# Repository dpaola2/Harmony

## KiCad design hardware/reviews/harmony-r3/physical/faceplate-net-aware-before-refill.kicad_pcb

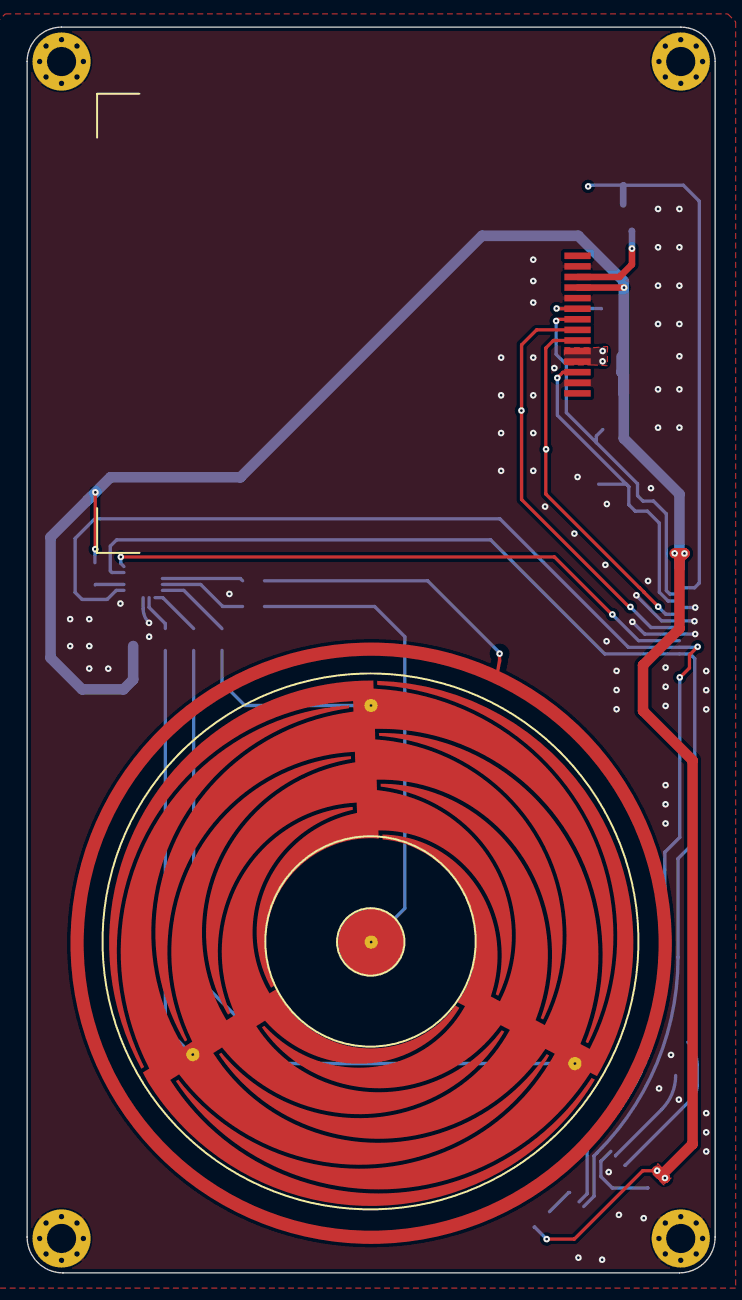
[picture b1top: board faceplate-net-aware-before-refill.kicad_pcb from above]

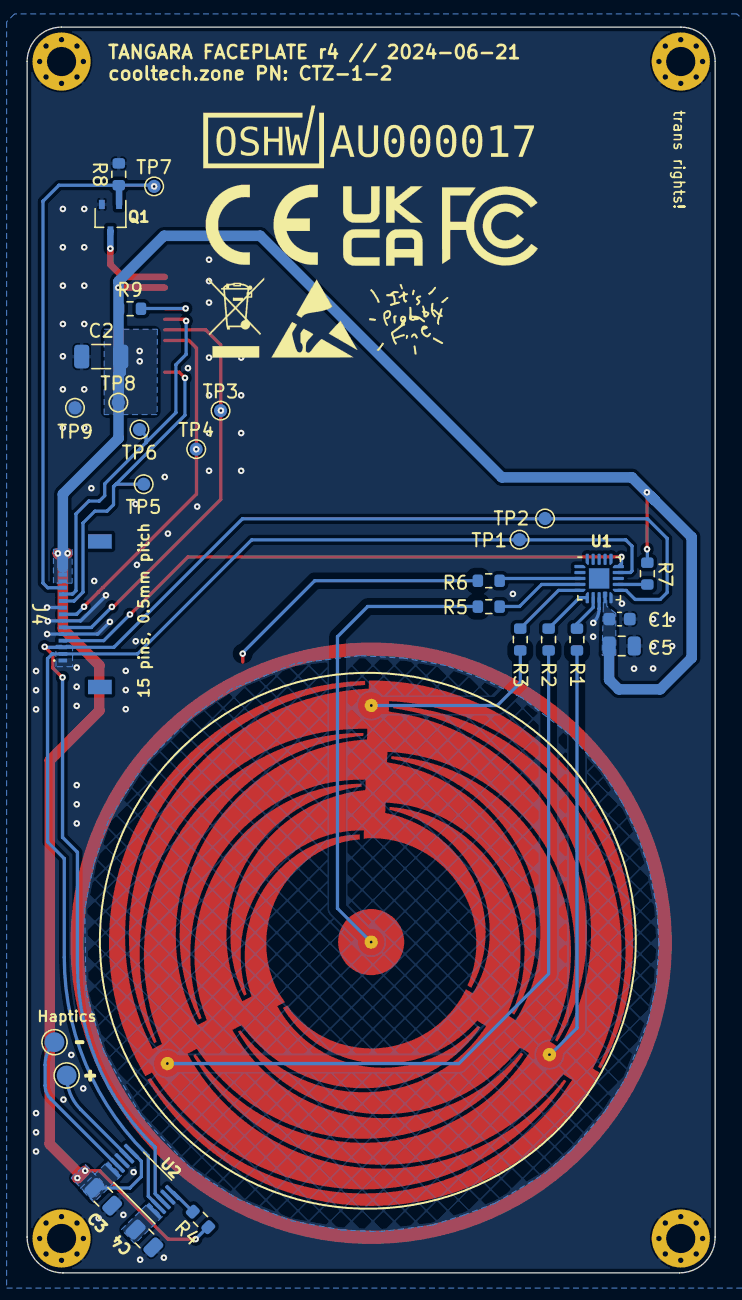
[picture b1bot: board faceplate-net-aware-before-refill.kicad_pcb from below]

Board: 2 copper layers, 52.0 x 94.2 mm, 39 parts (31 on the bottom side), 27 nets.

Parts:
C1: 0.1uF; C_0603_1608Metric
C2: 22uF; C_1206_3216Metric
C3, C4, C5: 1uF; C_0805_2012Metric
H1, H2, H3, H4: MountingHole; MountingHole_2.2mm_M2_Pad_Via
J1: +; TestPoint_Pad_D1.5mm
J2: -; TestPoint_Pad_D1.5mm
J4: MB Connector; G-Switch GT-F0509SR15-15SMT01
LCD1: JD-T1800
Q1: PJC138K; SOT-323_SC-70
R1, R2, R3, R4, R5, R6, R7, R9: 10k; R_0603_1608Metric
R8: 1M; R_0603_1608Metric
SW1: BUTTON; qtouch-button
SW2: WHEEL; qtouch-wheel
SW3: GUARD; qtouch-guard
TP1: SCL; TestPoint_Pad_D1.0mm
TP2: SDA; TestPoint_Pad_D1.0mm
TP3: PICO; TestPoint_Pad_D1.0mm
TP4: SCLK; TestPoint_Pad_D1.0mm
TP5: CS; TestPoint_Pad_D1.0mm
TP6: RS; TestPoint_Pad_D1.0mm
TP7: LED; TestPoint_Pad_D1.0mm
TP8: 3V3; TestPoint_Pad_D1.0mm
TP9: GND; TestPoint_Pad_D1.0mm
U1: AT42QT2120; VQFN-20-1EP_3x3mm_P0.45mm_EP1.55x1.55mm
U2: DRV2605LDGS; VSSOP-10_3x3mm_P0.5mm
kibuzzard-63E31E51: G***; kibuzzard-63E31E51
kibuzzard-63E31E57: G***; kibuzzard-63E31E57

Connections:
+3V3: C1.1, C2.1, C3.2, C5.2, J4.13, J4.14, J4.15, LCD1.4 (LEDA), LCD1.10 (VCC), LCD1.11 (VCC2), R4.1, R7.2, R9.1, TP8.1, U1.9 (VDD), U2.6 (VDD/NC), U2.10 (VDD)
/CS: J4.10, LCD1.12 (CS), TP5.1
/LED_ENABLE: J4.12, Q1.1 (G), R8.1, TP7.1
/PICO: J4.6, LCD1.8 (DATA), TP3.1
/RS: J4.11, LCD1.7 (RS/DC), TP6.1
/SCL: J4.2, TP1.1, U1.14 (SCL), U2.2 (SCL)
/SCLK: J4.8, LCD1.9 (CLOCK), TP4.1
/SDA: J4.3, TP2.1, U1.11 (SDA), U2.3 (SDA)
/TOUCH_INT: J4.4, U1.15 (~CHANGE)
GND: C1.2, C2.2, C3.1, C4.1, C5.1, H1.1, H2.1, H3.1, H4.1, J4.1, J4.5, J4.7, J4.9, LCD1.2 (GND), LCD1.5 (GND1), LCD1.13 (GND2), Q1.2 (S), R8.2, TP9.1, U1.8 (VSS), U1.10 (MODE), U2.4 (IN/TRIG), U2.8 (GND)
unnamed: J1.1, U2.7 (OUT+)
unnamed: J2.1, U2.9 (OUT-)
unnamed: LCD1.3 (LEDK), Q1.3 (D)
unnamed: LCD1.6 (RESET), R9.2
unnamed: R5.1, SW1.1
unnamed: R1.1, SW2.1
unnamed: R2.1, SW2.2
unnamed: R3.1, SW2.3
unnamed: R6.1, SW3.1
unnamed: R1.2, U1.7 (KEY0)
unnamed: R2.2, U1.6 (KEY1)
unnamed: R3.2, U1.5 (KEY2)
unnamed: R5.2, U1.4 (KEY3)
unnamed: R6.2, U1.3 (KEY4)
unnamed: R7.1, U1.12 (~RESET)
unnamed: R4.2, U2.5 (EN)
unnamed: C4.2, U2.1 (REG)

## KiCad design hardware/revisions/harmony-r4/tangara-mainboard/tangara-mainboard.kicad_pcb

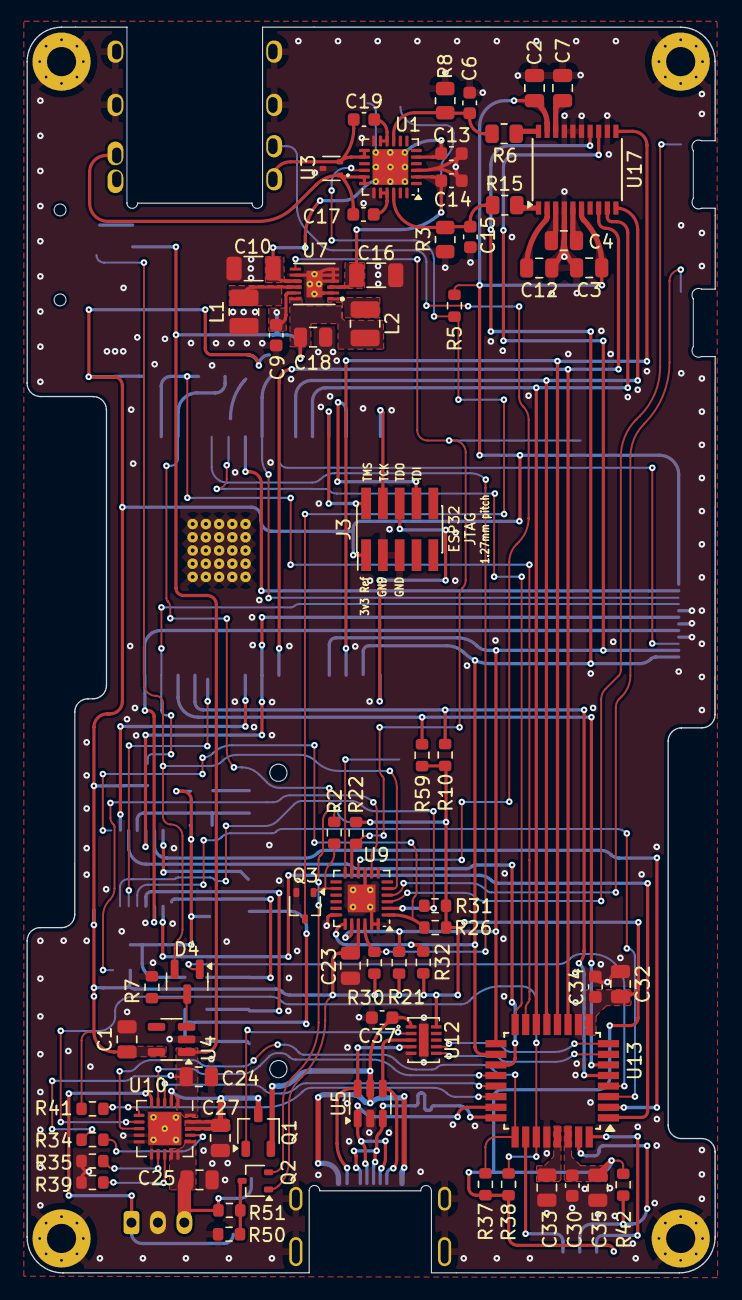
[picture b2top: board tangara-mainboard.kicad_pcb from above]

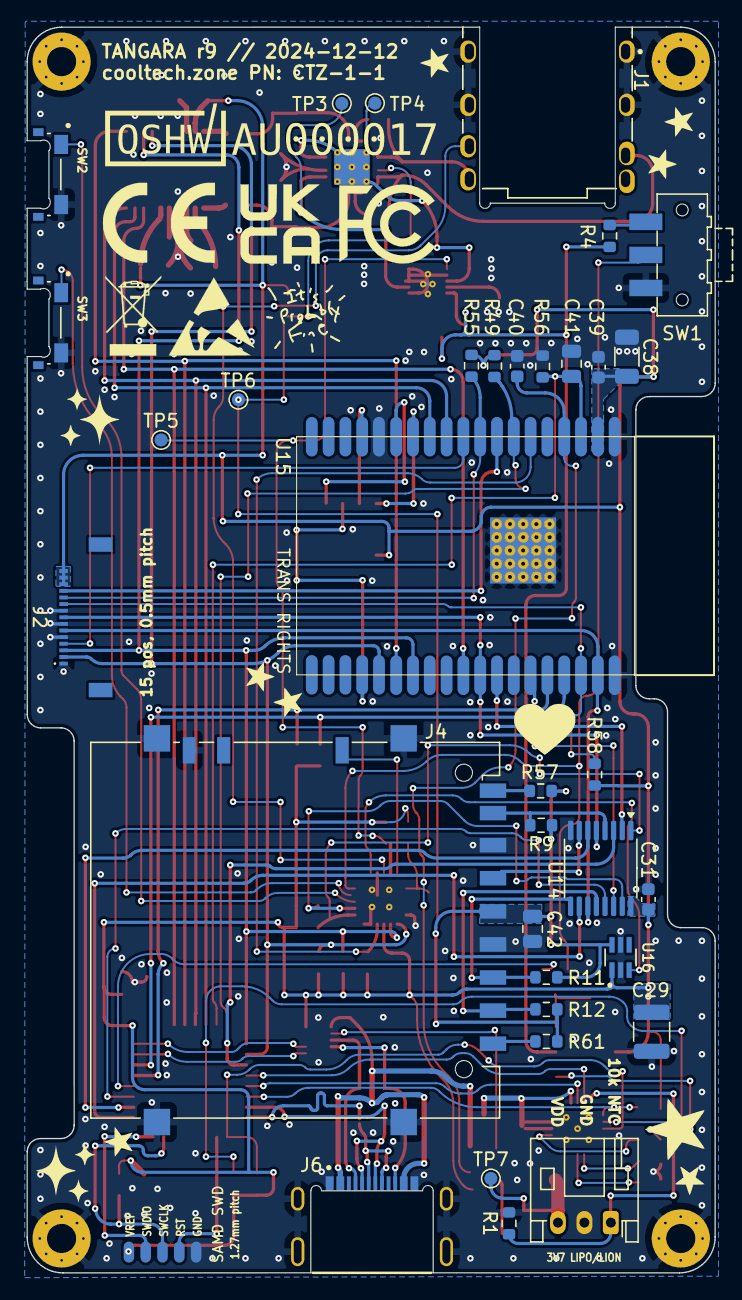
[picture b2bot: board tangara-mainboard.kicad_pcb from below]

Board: 4 copper layers, 52.0 x 94.2 mm, 106 parts (35 on the bottom side), 92 nets.

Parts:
C1, C2, C3, C7, C18, C24, C25, C27, C32, C35, C42: 10μF; C_0805_2012Metric
C4, C12, C23, C33, C41: 1μF; C_0805_2012Metric
C6, C15: 2700pF; C_0603_1608Metric
C9, C13, C14, C30, C31, C34, C37, C39, C40: 0.1μF; C_0603_1608Metric
C10, C16, C38: 22μF; C_1206_3216Metric
C17, C19: 100pF; C_0603_1608Metric
C29: 100uF; C_1210_3225Metric
D4: BAT54C; SOT-23
H1, H2, H3, H4: MountingHole; MountingHole_2.2mm_M2_Pad_Via2
J1: SJ-3506-SMT; CUI_SJ-3506-SMT
J2: FP Connector; G-Switch GT-F0509SR15-15SMT01
J3: JTAG; PinHeader_2x05_P1.27mm_Vertical_SMD
J4: SD_Card; SD_Hirose_DM1AA_SF_PEJ82
J5: SWD; SAMDSWD
J6: USB; GCT_USB4510-03-1-A_REVA
J7: Battery; JST_PH_S3B-PH-K_1x03_P2.00mm_Horizontal
L1, L2: 4.7μH; L_1008_2520Metric
Q1: PMV48XPA2R; TSOT-23
Q2, Q3: PJC138K; SOT-323_SC-70
R1, R2, R4, R5, R9, R10, R11, R12, R21, R22, R26, R30, R31, R32, R34, R35, R37, R38, R41, R49, R55, R57, R58, R59, R61: 10kΩ; R_0603_1608Metric
R3, R8: 2.2kΩ; R_0805_2012Metric
R6, R15: 560Ω; R_0805_2012Metric
R7, R50, R51, R56: 1MΩ; R_0603_1608Metric
R39, R42: 1kΩ; R_0603_1608Metric
SW1: SW_SPDT; SW_SPDT_CK-JS102011SAQN
SW2, SW3: SW_Push; SW_EVQ-P4HB3B
TP3: +5V; TestPoint_Pad_D1.0mm
TP4: -5V; TestPoint_Pad_D1.0mm
TP5: AMP_EN; TestPoint_Pad_D1.0mm
TP6: AMP_MUTE; TestPoint_Pad_D1.0mm
TP7: BAT; TestPoint_Pad_D1.0mm
U1: INA1620; QFN-24-1EP_4x4mm_P0.5mm_EP2.7x2.7mm_ThermalVias
U3: D5V0L2B3T-7; SOT-523
U4: TLV75533PDBV; SOT-23-5
U5: PE1605C4A6; SOT-23-6
U7: TPS65133; SON40P300X300X80-13N
U9: PCA8575; HVQFN-24-1EP_4x4mm_P0.5mm_EP2.1x2.1mm
U10: MCP73871; QFN-20-1EP_4x4mm_P0.5mm_EP2.5x2.5mm_ThermalVias2
U12: BD91N01NUX; BD91N01NUX-E2
U13: ATSAMD21E18A-AF; TQFP-32_7x7mm_P0.8mm
U14: 74CBTLV3257; TSSOP-16_4.4x5mm_P0.65mm
U15: ESP32-WROVER-E; ESP32-WROVER
U16: TPS22948; SOT65P210X110-6N
U17: WM8523; SSOP-20_4.4x6.5mm_P0.65mm

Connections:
3.5mm_DETECT: J1.4, U9.10 (IO1_0)
+3V3: C1.1, C2.2, C3.1, C23.1, C29.1, C30.1, C31.1, C32.2, C34.1, C35.2, C38.1, C39.1, J2.13, J2.14, J2.15, J3.1 (vRef), J5.1, Q2.1 (G), R2.2, R5.1, R10.1, R21.1, R22.2, R26.1, R30.1, R31.1, R32.1, R37.1, R38.1, R41.1, R42.1, R49.1, R55.1, R58.1, R59.1, U4.5 (OUT), U9.21 (VDD), U12.10 (VDD_IO), U13.9 (VDDANA), U13.30 (VDDIN), U14.16 (VCC), U15.2 (VDD), U16.1 (IN), U17.6 (LINEVDD), U17.19 (AVDD)
+5VA: C14.1, C16.1, TP3.1, U1.2 (V+), U7.3 (VPOS)
-5VA: C10.2, C13.1, TP4.1, U1.5 (V-), U1.25 (EP), U7.9 (VNEG)
/ESP_EN: C41.1, R56.2, U13.15 (PA14), U15.3 (EN)
/JTAG.TCK: J3.4 (TCK), U15.16 (JTAG.TCK)
/JTAG.TDI: J3.8 (TDI), U15.14 (JTAG.TDI)
/JTAG.TDO: J3.6 (TDO), U15.23 (JTAG.TDO)
/JTAG.TMS: J3.2 (TMS), U15.13 (JTAG.TMS)
/Power/NTC: J7.1, R1.1, U10.5 (THERM)
/Power/VBUS_SWITCHED: C27.1, Q1.3 (D), U10.2 (VPCC), U10.18 (IN), U10.19 (IN)
/SWD.RESET: J5.4, U13.26 (~RESET)
/SWD.SWCLK: J5.3, R42.2, U13.31 (SWCLK)
/SWD.SWDIO: J5.2, U13.32 (SWDIO)
/UART.ESP.RX: R10.2, U13.5 (PA04(SERCOM0.0)), U15.34 (UART.RX)
/UART.ESP.TX: R59.2, U13.6 (PA05(SERCOM0.1)), U15.35 (UART.TX)
/~SAMD_INT: R49.2, U13.16 (PA15), U15.7 (I35)
AMP_EN: R22.1, TP5.1, U7.7 (EN), U9.11 (IO1_1)
AMP_MUTE: Q3.3 (D), R5.2, TP6.1, U1.16 (EN)
BAT_LEVEL: C40.2, Q2.2 (S), U15.4 (ADC1_CH0/NOINT)
CHG_PROG: U10.4 (PROG2), U13.20 (PA19)
CHG_SEL: U10.3 (SEL), U13.21 (PA22)
CHG_STAT1: R37.2, U10.8 (STAT1/~LBO), U13.25 (PA27)
CHG_STAT2: R38.2, U10.7 (STAT2), U13.27 (PA28)
DAC.BCK: U13.13 (PA10(I2S/SCK)), U15.11 (I2S.BCK), U17.10 (BCLK)
DAC.DATA: U13.11 (PA08(I2S/SD)), U15.29 (I2S.DOUT), U17.8 (DACDAT)
DAC.LRCK: U13.14 (PA11(IS2/FS)), U15.12 (I2S.LRCK), U17.9 (LRCLK)
DAC.MCK: U13.12 (PA09(I2S/MCK)), U15.25 (BOOT/I2S.SCK), U17.11 (MCLK)
DISPLAY_DR: J2.11, R55.2, U15.9 (IO33)
DISPLAY_LED_EN: J2.12, U15.8 (IO32)
ESP_SPI.DISPLAY_CS: J2.10, R58.2, U15.36 (SPI.CS1)
ESP_SPI.PICO: J2.6, U14.11, U15.37 (SPI.PICO)
ESP_SPI.POCI: U14.2, U15.31 (SPI.POCI)
ESP_SPI.SCLK: J2.8, U14.5, U15.30 (SPI.CLK)
ESP_SPI.SD_CS: U14.14, U15.33 (SPI.CS0)
GND: C1.2, C2.1, C3.2, C6.1, C7.2, C9.2, C10.1, C12.1, C13.2, C14.2, C15.1, C16.2, C18.2, C23.2, C24.2, C25.2, C27.2, C29.2, C30.2, C31.2, C32.1, C33.1, C34.2, C35.1, C37.2, C38.2, C39.2, C40.1, C41.2, C42.2, H1.1, H2.1, H3.1, H4.1, J1.1, J1.5, J1.SH1, J1.SH2, J2.1, J2.5, J2.7, J2.9, J3.3 (GND), J3.5 (GND), J4.3 (VSS), J4.6 (VSS), J4.SH, J4.SW, J5.5, J6.A1_B12 (GND), J6.B1_A12 (GND), J6.S1 (SHELL_GND), J6.S2 (SHELL_GND), J6.S3 (SHELL_GND), J6.S4 (SHELL_GND), J7.2, L1.1, Q3.2 (S), R1.2, R3.1, R7.1, R8.1, R35.2, R39.2, R50.2, R56.1, SW1.1 (A), SW2.2, SW3.2, U1.3 (GND), U1.12, U1.19, U3.3, U4.2 (GND), U5.2 (GND), U7.2 (PGND), U7.4 (GND), U7.5 (AGND), U7.6 (GND), U7.8 (GND), U7.13 (EXP), U9.9 (VSS), U9.18 (A0), U9.23 (A1), U9.24 (A2), U9.25 (EP), U10.9 (~TE), U10.10 (V_{SS}), U10.11 (V_{SS}), U10.21 (V_{SS}), U12.5 (GND), U12.11 (EP), U13.10 (GND), U13.28 (GND), U14.8 (GND), U15.1 (GND), U15.15 (GND), U15.38 (GND), U15.39 (GND), U16.2 (GND), U16.5 (FLT), U17.4 (LINEGND), U17.12 (SDOUT/DEEMPH), U17.15 ({~CS}/{~MUTE}), U17.16 (CIFMODE), U17.17 (AGND)
I2C.SCL: J2.2, R26.2, U9.19 (SCL), U13.18 (PA17(SERCOM3.1)), U15.24 (I2C.SCL), U17.14 (SCLK)
I2C.SDA: J2.3, R21.2, U9.20 (SDA), U13.17 (PA16(SERCOM3.0)), U15.26 (I2C.SDA), U17.13 (SDA)
KEY_LOCK: D4.2, SW1.2 (B), U9.5 (IO0_4)
KEY_VOL_DOWN: SW3.1, U9.4 (IO0_3)
KEY_VOL_UP: SW2.1, U9.3 (IO0_2)
unnamed: C17.2, J1.2, U1.17, U1.18, U3.1
unnamed: C19.2, J1.3, U1.13, U1.14, U3.2
unnamed: J4.1 (CD/DAT3), R12.2, U14.12
unnamed: J4.5 (CLK), U14.7
unnamed: J4.2 (CMD), R11.2, U14.9
unnamed: J4.7 (DAT0), R9.2, U14.4
unnamed: J4.8 (DAT1), R57.2
unnamed: J4.9 (DAT2), R61.2
unnamed: C42.1, J4.4 (VDD), R9.1, R11.1, R12.1, R57.1, R61.1, U16.6 (OUT)
unnamed: J6.A5 (CC1), U5.4 (IO3), U12.3 (CC1)
unnamed: J6.B5 (CC2), U5.6 (IO5), U12.4 (CC2)
unnamed: C25.1, J7.3, R51.1, TP7.1, U10.14 (V_{BAT}), U10.15 (V_{BAT}), U10.16 (V_{BAT_SENSE})
unnamed: Q1.1 (G), U12.2 (SWDRV)
unnamed: Q2.3 (D), R50.1, R51.2
unnamed: Q3.1 (G), R2.1, U9.14 (IO1_4)
unnamed: R4.1, SW1.3 (C)
unnamed: C15.2, R3.2, R15.2, U1.22 (+)
unnamed: C17.1, U1.20, U1.21 (-)
unnamed: C6.2, R6.2, R8.2, U1.9 (+)
unnamed: C19.1, U1.10 (-), U1.11
unnamed: D4.3, R7.2, U4.3 (EN)
unnamed: L1.2, U7.10 (SWN)
unnamed: L2.1, U7.1 (SWP)
unnamed: R34.2, U10.17 (CE)
unnamed: R39.1, U10.13 (PROG1)
unnamed: R35.1, U10.12 (PROG3)
unnamed: C33.2, U13.29 (VDDCORE)
unnamed: R32.2, U9.1 (IO0_0), U14.1 (S)
unnamed: R31.2, U9.2 (IO0_1), U14.15 (~OE)
unnamed: C4.1, U17.5 (CPCA)
unnamed: C4.2, U17.3 (CPCB)
unnamed: C12.2, U17.2 (CPVOUTN)
unnamed: R15.1, U17.1 (LINEVOUTL)
unnamed: R6.1, U17.20 (LINEVOUTR)
unnamed: C7.1, U17.18 (VMID)
SAMD_SPI.CS: U13.3 (PA02), U14.13
SAMD_SPI.PICO: U13.1 (PA00(SERCOM1.0)), U14.10
SAMD_SPI.POCI: U13.19 (PA18(SERCOM1.2)), U14.3
SAMD_SPI.SCLK: U13.2 (PA01(SERCOM1.1)), U14.6
SD_CD: J4.CP, U9.12 (IO1_2)
SYS_POWER: C9.1, C18.1, C24.1, L2.2, R4.2, R34.1, U4.1 (IN), U7.11 (AVIN), U7.12 (PVIN), U10.1 (OUT), U10.20 (OUT)
SYS_PWR_EN_SAMD: D4.1, U13.4 (PA03)
USB.DN: J6.A7 (DN), J6.B7 (DN), U5.1 (IO1), U13.23 (USB.DM)
USB.DP: J6.A6 (DP), J6.B6 (DP), U5.3 (IO2), U13.24 (USB.DP)
USB_TCC0: U12.7 (TCC0), U13.8 (PA07)
USB_TCC1: U12.6 (TCC1), U13.7 (PA06)
VBUS: C37.1, J6.A4_B9 (VBUS), J6.B4_A9 (VBUS), Q1.2 (S), U5.5 (IO4), U12.1 (VBUS)
~CHG_PWR_OK: R41.2, U10.6 (~PG), U13.22 (PA23)
~GPIO_INT: R30.2, U9.22 (~INT), U15.6 (I34)
~SD_VDD_EN: U9.8 (IO0_7), U16.3 (ON)
~TOUCH_INT: J2.4, U15.10 (IO25)

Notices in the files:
parts and their libraries:
Copyright 2021 Accelerated Designs. All rights reserved.
